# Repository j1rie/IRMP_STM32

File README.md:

# IRMP on STM32 - a USB IR receiver/sender/power switch with wake-up timer

A remote control receiver with many functions based on cheap hardware.

## Introduction
For 2 € you can buy an ST-Link emulator or a STM32F103 development board, usually made in China, on ebay. The STM32F103 microcontroller on it is flashed with an open source firmware with many functions.

## Features
* connection over USB 
* registers as HID device, appears as /dev/hidraw or "Custom HID device", no drivers needed
* transfers the data over USB2 in hardware at fullspeed 
* IR receiver (about 40 protocols decoded in hardware) 
* power on PC via remote control from S3 (STR) and S4 (STD) via USB or from S3, S4 and S5 (SoftOff) via motherboard switch (+5V required, on USB or from PSU or motherboard) 
* power on PC via built-in timer from S3 (STR) and S4 (STD) via USB or from S3, S4 and S5 (SoftOff) via motherboard switch (+5V required, on USB or from PSU or motherboard) 
* IR transmitter (about 40 protocols) 
* the configuration is stored in the emulated eeprom
* bootloader for easy firmware update
* macro support

A macro allows a sequence of IR commands to be sent via the transmitter diode when a trigger is received.
 macroslot0 is the trigger, macroslot1 … macroslot7 are the commands to be sent.

## Software Linux
* GUI configuration tool stm32IRconfig_gui for configuration: set, get and reset wakeup codes, macros, alarm time, send IR and show the received IR code. It is possible to program wakeups and macros by the remote control. Create, test and edit the translation table using remote control and mouse. Comprehensive debug messages. Firmware update.
* interactive command line program stm32IRconfig for configuration: set, get and reset wakeups, macros, alarm time, send IR and display the received IR code. It is possible to program wakeups and macros by the remote control.
* stm32IRalarm for setting and reading alarm time via script 
* stm32FWupgrade for command line firmware upgrade
* irmplircd is a daemon that runs in the background as an independent lirc server and passes the IR codes/events on to the application https://github.com/realglotzi/irmplircd
* irctl for configuration: https://github.com/olebowle/irctl
* Software available for Ubuntu, yaVDR, easyVDR, MLD.

## Software Windows
* GUI configuration tool stm32IRconfig_gui (same as linux)
* interactive command line programm stm32IRconfig (same as linux)
* stm32IRalarm to set and read alarm time via script
* stm32FWupgrade for command line firmware upgrade
* MediaPortal plugin: https://github.com/pikim/HIDIRT-host/tree/master/hidirt.MePo
* EventGhost with generic HID

## Creating a keymap
The stm32IRconfig_gui can be used to create a keymap using the remote control.  
There are two methods.  
  
(1)  
   
First method: Press "receive mode" and open the template keymap.
Click on the line with the name of the button, press the button on the remote, press "write IR" - repeat for all the buttons.  
  
(2)  
   
Second method: Press "receive mode".
Press the button on the remote, type the name of the button into the Key text box and press "append" - repeat for all the buttons.

You can now test the keymap: After pressing the button on the remote, the red cursor should be in the corresponding line.
When you are done, press "save" to save the keymap.

## Learning wakeup
If the first wakeup is empty, the first IR data received will be stored in the wakeup.  
Change wakeup with stm32kbdIRconfig_gui: press set by remote - wakeup, press button on remote control.  
Important for testing: wakeup only happens, if the PC is switched off.  
If the PC is powered on, only the key is sent to the PC (so you can use the same button to switch on and off).  

## EventGhost

A keycode in the left event window is dragged into the right configuration window and assigned to the desired action of a plugin. 

## Building from source
The sources are not complete until you run the prepare script, the script downloads the IRMP sources, extracts and patches the sources. You have to download the ST sources manually, because unfortunately you have to register.  
This makes it possible to put the patches under the GPL, without interfering with the original licences.  
It is also easier to see, what has been changed, too.  
Compile with arm-none-eabi-gcc.  

## Pin-Out
See /STM32Fxxxxx/src/config.h.

## Flashing the bootloader with a ST-Link
Connect  
Programmer SWDIO -> IO  
Programmer SWCLK -> CLK  
Programmer GND -> G  
Programmer 3V3 -> V3  
Windows:  
Get the STM32 ST-Link Utility.  
File - Open File - boot.blackDev.bin (https://github.com/j1rie/STM32F103-bootloader/tree/master/binaries)  
Target - Program & Verify (confirm a message about read out protection, if it appears)  
Linux:  
openocd -f ocd-program.cfg  
If the flash is locked, first run openocd -f ocd-unlock.cfg first, disconnect and reconnect the device, and then 
run openocd -f ocd-program.cfg again.  
The files are in the STM32Fxxx(yy)-bootloader repos.  
https://github.com/j1rie/IRMP_STM32_KBD/wiki/Herstellungsprozess-Schwarze#bootloader-flashen  

## Flashing the firmware
Disconnect from USB.  
Linux: Start ./stm32FWupgrade ./2019-07-06_16-32_blackDev_BL_SC_jrie.bin  
Windows: Start stm32FWupgrade.exe 2020-02-15_00-29_blueDev_BL_SC_jrie.bin  
Attach to USB.  
Instead of stm32FWupgrade you can use stm32IRconfig_gui.  
https://github.com/j1rie/IRMP_STM32_KBD/wiki/Herstellungsprozess-Schwarze#firmware-flashen  

## Other ways how to flash
Flashing with an USB-serial-TTL is possible on the developer boards.  
Flashing over USB is possible on the boards, that support it.  
See https://www.mikrocontroller.net/articles/IRMP_auf_STM32_-_ein_USB_IR_Empf%C3%A4nger/Sender/Einschalter_mit_Wakeup-Timer#Firmware_Flashing  

## irmplircd, eventlircd, udev and systemd
See /irmplircd/README.

## Schematics
https://datasheets.raspberrypi.com/pico/pico-datasheet.pdf  
https://datasheets.raspberrypi.com/pico/pico-2-datasheet.pdf  
https://files.waveshare.com/upload/4/4c/RP2040_Zero.pdf  
https://files.waveshare.com/upload/9/90/RP2040-One.pdf  
https://files.seeedstudio.com/wiki/XIAO-RP2350/res/Seeed-Studio-XIAO-RP2350-v1.0.pdf  

## Thanks to
Frank Meyer for IRMP. [1]  
Uwe Becker for adapting IRMP to the STM32F4xx and his USB-HID for the STM32F4xx. [2]  
His work helped me to get started with the STM32F105.  
Andrew Kambaroff for his USB-HID for the STM32F103. [3]  
His work helped me to get started with the STM32F103.  
Ole Ernst for code review, linux Makefile and linux download-extract-patch-script and new protocol. [4]  
Manuel Reimer for gcc-4.9 fix, SimpleCircuit and check if host is running. [5]  
Martin Neubauer for integration into EasyVDR, addon board development and selling ready-to-use receiver sets. [6]  
Alexander Grothe for integration into yaVDR and much help with difficult questions. [7]  
Helmut Emmerich for selling ready-to-use receiver sets and user support. [8]  
Claus Muus for integration into MLD. [9]  
Bernd Juraschek for vdr-plugin-statusleds, which was the base for vdr-plugin-statusleds2irmphidkbd. [10]  
All Users for questions, feature requests, feedback and ideas.  

[1] https://www.mikrocontroller.net/articles/IRMP  
[2] http://mikrocontroller.bplaced.net/wordpress/?page_id=744  
[3] https://habr.com/post/208026/  
[4] https://github.com/olebowle  
[5] https://github.com/M-Reimer  
[6] https://www.vdr-portal.de/user/4786-ranseyer/, https://github.com/ranseyer/STM32-IRMP-Hardware  
[7] https://www.vdr-portal.de/user/24681-seahawk1986/  
[8] https://www.vdr-portal.de/user/13499-emma53/  
[9] https://www.vdr-portal.de/user/942-clausmuus/  
[10] <statusleds@bjusystems.de>  

## Discussion and further information
Comments, questions and suggestions can be sent to https://www.vdr-portal.de/forum/index.php?thread/123572-irmp-auf-stm32-ein-usb-ir-empf%C3%A4nger-sender-einschalter-mit-wakeup-timer/

## Construction manuals
https://github.com/j1rie/IRMP_STM32_KBD/wiki/Herstellungsprozess-Schwarze  
https://www.mikrocontroller.net/articles/IRMP_auf_STM32_%E2%80%93_stark_vereinfachte_Bauanleitung  
https://www.mikrocontroller.net/articles/IRMP_auf_STM32_-_Bauanleitung  
The latter two are also in /doc/old.  

Have fun with IRMP on STM32!

Copyright (C) 2014-2025 Jörg Riechardt

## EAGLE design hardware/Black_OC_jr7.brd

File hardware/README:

There are different hardware designs for the sticks.
Make sure that the extension board fits your stick.

Stick1_jr1 is based on:
https://github.com/ranseyer/STM32-IRMP-Hardware/tree/master/1_Small_ST-Link/STl-Link-V303-small.brd
https://github.com/ranseyer/STM32-IRMP-Hardware/tree/master/1_Small_ST-Link/STl-Link-V303-small.sch

I highly recommend the optocoupler version. It is not very likely that you will actually need it, but
if you do have a motherboard, that needs it, it will save you a lot of debugging effort.

If you like a tiny design, have a look at https://github.com/Sl-Alex/IRMP_STM32_MINI and at
https://www.vdr-portal.de/index.php?attachment/48154-20230825-130009-jpg/

In case you want to attach a 4 digit display tm1637, connect:
GND - GND, 5V - 5V, DIO - B11, CLK - B4, see st32tm1637.h.

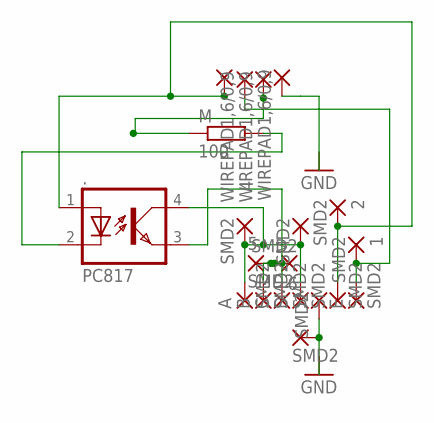
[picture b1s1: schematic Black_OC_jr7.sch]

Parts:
1, 2, 4, 5, 6, ...: SMD2; SMD1,27-2,54
+: SMD2; SMD1,27-2,54
-: SMD2; SMD1,27-2,54
--: 1,6/0,9
---: WIREPAD1,6/0,9; 1,6/0,9
----: WIREPAD1,6/0,9; 1,6/0,9
-----: WIREPAD1,6/0,9; 1,6/0,9
.: PC817; DIL04
A: SMD2; SMD1,27-2,54
B: SMD2; SMD1,27-2,54
C: SMD2; SMD1,27-2,54
D: SMD2; SMD1,27-2,54
E: SMD2; SMD1,27-2,54
M: 100; 0204/7
PAD7: SMD2; SMD1,27-2,54

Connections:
GND: -.1, -----.1, PAD7.1
unnamed: ----.1, M.1
unnamed: 4.1, ..4 (COL), ....1, A.1, D.1
unnamed: 5.1, 6.1, ..3 (EMIT), B.1, C.1
unnamed: 2.1, +.1, --.1, ..1 (A)
unnamed: 1.1, ---.1, E.1
unnamed: ..2 (C), M.2

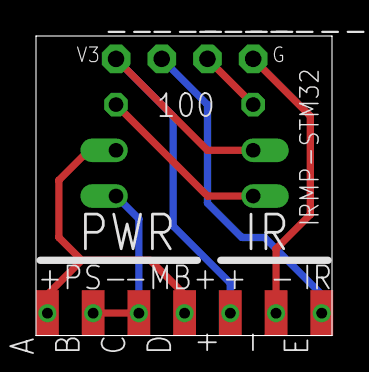
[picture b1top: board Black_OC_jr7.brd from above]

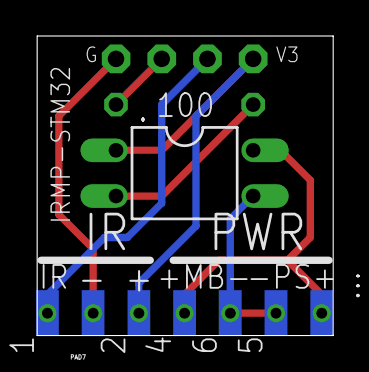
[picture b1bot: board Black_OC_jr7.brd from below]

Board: 2 copper layers, 16.4 x 16.6 mm, 20 parts (8 on the bottom side), 7 nets.

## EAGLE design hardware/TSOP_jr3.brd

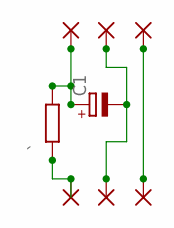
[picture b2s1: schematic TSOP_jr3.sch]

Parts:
": 1,6/0,9
"": 1,6/0,9
""": 1,6/0,9
...., ....., ......: 1,6/0,9
C1: CPOL-EUE1.8-4; E1,8-4
`: R-EU_0204/5; 0204/5

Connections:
unnamed: ".1, .......1
unnamed: "".1, ......1, C1.-
unnamed: """.1, C1.+, `.2
unnamed: .....1, `.1

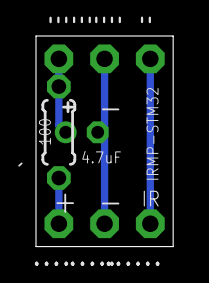
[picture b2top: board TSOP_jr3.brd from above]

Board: 2 copper layers, 7.6 x 11.7 mm, 8 parts (0 on the bottom side), 4 nets.

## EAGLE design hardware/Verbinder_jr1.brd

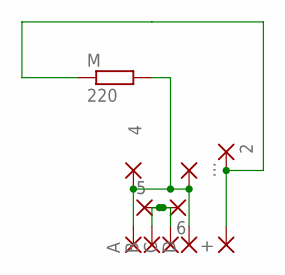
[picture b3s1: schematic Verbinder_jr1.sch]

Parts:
2, 4, 5, 6, ...: SMD2; SMD1,27-2,54
+: SMD2; SMD1,27-2,54
A: SMD2; SMD1,27-2,54
B: SMD2; SMD1,27-2,54
C: SMD2; SMD1,27-2,54
D: SMD2; SMD1,27-2,54
M: 220; 0204/7

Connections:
unnamed: 2.1, +.1, M.1
unnamed: 4.1, ....1, A.1, D.1, M.2
unnamed: 5.1, 6.1, B.1, C.1

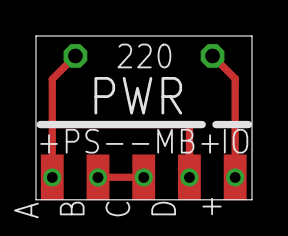
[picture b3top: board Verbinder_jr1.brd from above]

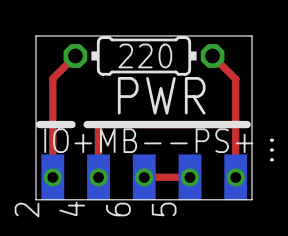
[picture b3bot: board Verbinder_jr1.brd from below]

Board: 2 copper layers, 12.0 x 9.1 mm, 11 parts (6 on the bottom side), 3 nets.

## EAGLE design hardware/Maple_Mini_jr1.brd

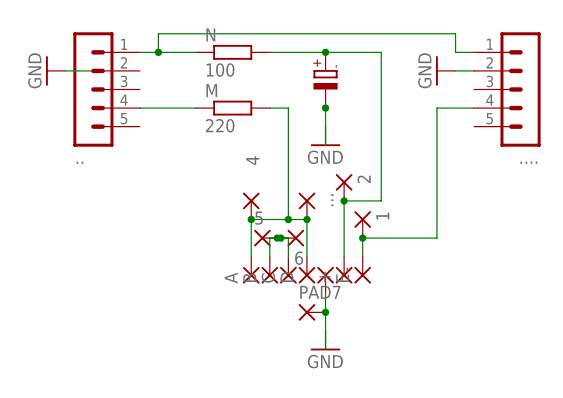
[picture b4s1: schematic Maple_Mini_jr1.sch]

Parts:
1, 2, 4, 5, 6, ...: SMD2; SMD1,27-2,54
+: SMD2; SMD1,27-2,54
-: SMD2; SMD1,27-2,54
.: CPOL-EUE1.8-4; E1,8-4
.., ....: MA05-1
A: SMD2; SMD1,27-2,54
B: SMD2; SMD1,27-2,54
C: SMD2; SMD1,27-2,54
D: SMD2; SMD1,27-2,54
E: SMD2; SMD1,27-2,54
M: 220; 0204/7
N: 100; 0204/7
PAD7: SMD2; SMD1,27-2,54

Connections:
GND: -.1, ..-, .....2, PAD7.1
unnamed: ...1, .....1, N.1
unnamed: ...4, M.1
unnamed: 4.1, ....1, A.1, D.1, M.2
unnamed: 5.1, 6.1, B.1, C.1
unnamed: 2.1, +.1, ..+, N.2
unnamed: 1.1, .....4, E.1

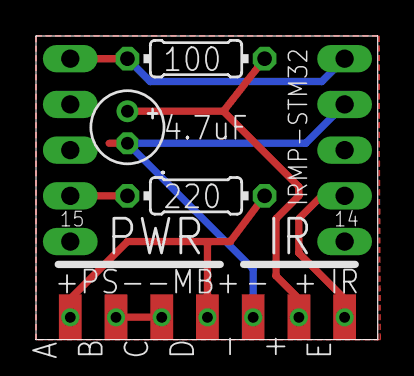
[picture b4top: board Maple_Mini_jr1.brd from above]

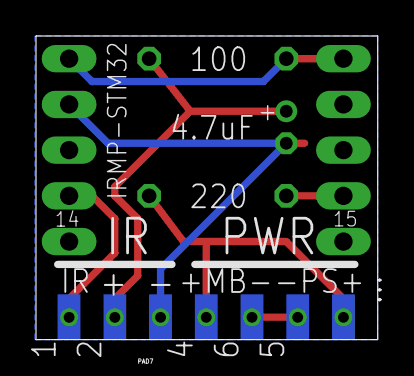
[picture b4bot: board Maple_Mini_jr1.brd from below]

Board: 2 copper layers, 19.0 x 16.9 mm, 19 parts (7 on the bottom side), 7 nets.

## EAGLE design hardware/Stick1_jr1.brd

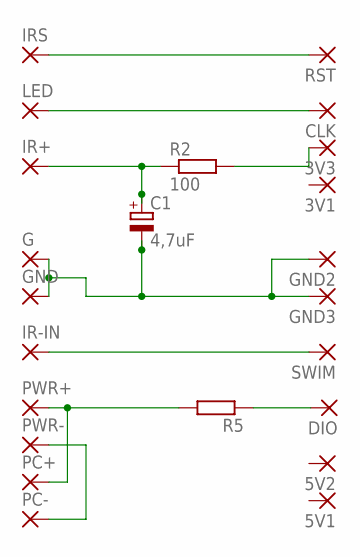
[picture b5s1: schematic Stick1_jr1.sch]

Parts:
3V1, 3V3, 5V1, 5V2: SMD2; SMD1,27-2,54
C1: 4,7uF; E1,8-4
CLK: SMD2; SMD1,27-2,54
DIO: SMD2; SMD1,27-2,54
G: SMD2; SMD1,27-2,54
GND, GND2, GND3: SMD2; SMD1,27-2,54
IR+: SMD2; SMD1,27-2,54
IR-IN: SMD2; SMD1,27-2,54
IRS: SMD2; SMD1,27-2,54
LED: SMD2; SMD1,27-2,54
PC+: SMD2; SMD1,27-2,54
PC-: SMD2; SMD1,27-2,54
PWR+: SMD2; SMD1,27-2,54
PWR-: SMD2; SMD1,27-2,54
R2: 100; 0204/7
R5: R-EU_0204/7; 0204/7
RST: SMD2; SMD1,27-2,54
SWIM: SMD2; SMD1,27-2,54

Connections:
unnamed: 3V3.1, R2.2
unnamed: C1.+, IR+.1, R2.1
unnamed: PC-.1, PWR-.1
unnamed: PC+.1, PWR+.1, R5.2
unnamed: DIO.1, R5.1
unnamed: CLK.1, LED.1
unnamed: IRS.1, RST.1
unnamed: IR-IN.1, SWIM.1
unnamed: C1.-, G.1, GND.1, GND2.1, GND3.1

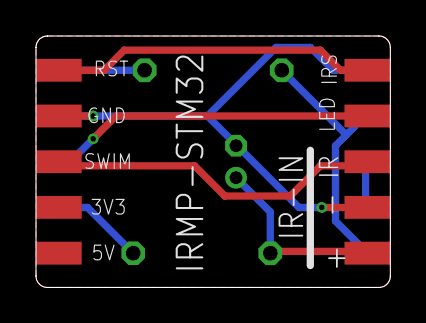
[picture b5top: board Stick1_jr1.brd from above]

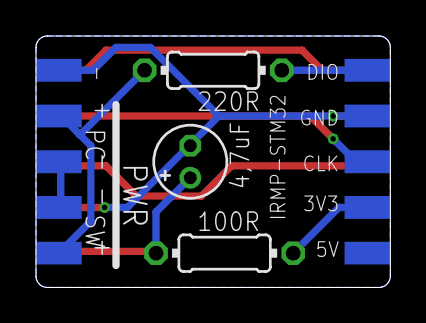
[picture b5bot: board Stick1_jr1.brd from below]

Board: 2 copper layers, 19.7 x 14.0 mm, 23 parts (13 on the bottom side), 9 nets.

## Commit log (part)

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2018-08-28 small fixes in text
2018-10-03 transfer to F105
2018-10-15 RCMM added to default
2018-10-15 fix warning
2018-11-02 new compiler wants spaces
2019-02-11 parameter change in dfu-util
2019-02-13 reset eeprom and firmware by flashing zeros
2019-05-04 updated dfu-util binary
2019-06-13 the --shutdown line in vdr.conf points to the shutdown script
2019-07-04 vdrshutdown example script
2019-07-06 removed forgotten line, improve irmpexec integration, make logging work
2019-07-06 imported more stuff from my mikrocontroller page into the README
2019-07-06 fix spelling
2019-07-06 formating
2019-07-06 spelling
2019-07-06 the F105 has been flashed so many times, that a new jumpaddress is necessary
2019-07-12 log only once
2019-07-12 improve description of macros
2019-07-12 make store_new_wakeup() faster
2019-07-13 point to github
2019-07-13 consume old IR before setting wakeup/macro by remote
2019-07-13 move 'consume old IR' into onReadIRcont()
2019-09-06 remove unneeded stuff from vdrshutdown script
2019-11-08 add ST-Link USB stick with unconnected PB11, fix typo, transfer to F105
2019-11-08 simplify ST-Link USB stick with unconnected PB11
2019-11-28 flashing bootloader and firmware
2019-11-28 link
2019-12-12 add F303 binaries
2019-12-12 adapt to F303
2019-12-14 fix eeprom and usb_hid patches
2019-12-20 make 'clean-objects' consistent
2019-12-20 make firmware string consistent
2020-01-22 use -ot instead of stat, exit with 1, thanks to @seahawk1986
2020-02-08 added connector board
2020-02-14 change blueDev pinout to blackdev pinout, firmwares, fix indentation
2020-02-15 recommend optocoupler
2020-02-18 add firmware flashing on Windows
2020-02-18 binaries
2020-02-26 pull from @a-v-s
2020-02-26 warn, if no STM32
2020-02-26 remove unneeded include
2020-03-04 fix error loop, when device gets disconnected, transfer to Windows, binaries
2020-04-16 added other ways of flashing
2020-04-18 remove ineffective attribute packed and unnecessary cast to enum
2020-04-22 linux gui: added firmware upgrade
2020-04-24 show update progress in gui as well, change pointer type
2020-04-25 indentation, one more sprintf
2020-04-29 change from libusb-0.1 to libusb-1.0
2020-05-01 change to USB-FS-Device_Lib_V4.1.0: adapt patches and script
2020-05-01 remove TODOs
2020-05-01 get wTransferSize from device instead from firmwae string
2020-05-07 collect messages which are to fast for gui, output to console too
2020-05-09 pointer argument for Upgrade needs to live longer, start thread earlier, initialize Upgrade, cleanup
2020-05-09 sleep not needed under linux
2020-05-20 loop longer in Write_and_Check(), silence warning, zstd needed for MSYS2 in Makefile, remove-O0 and -MD from Makefile, PATHSEP already defined, disconnect before rescan, show non-.bin files fully, Ct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
2020-05-20 tell used gcc-arm-none-eabi version, silence warning
2020-05-21 workaround for https://gcc.gnu.org/bugzilla/show_bug.cgi?id=83967, now newer gcc-arm-none-eabi versions do work
2020-05-21 initial start of stm32FWupgrade with files from @blacksphere/blackmagic/upgrade fetched Feb. 7, 2017
2020-05-21 change from libusb-0.1 to libusb-1.0, get wTransferSize from device, wait for device, firmwarefile as argument, remove -O0 and -MD from Makefile, remove unneeded includes
2020-05-22 binaries: stm32FWupgrade.exe, USB drivers for bootloader
2020-05-22 do without min(), merge includes for Windows and Linux
2020-05-27 no more sleep needed under Windows, simplify as bootloader is known, don't leak libusb_devices
2020-05-27 more simplify as bootloader is known, don't leak libusb_devices
2020-05-30 binaries, small fixes
2020-06-03 save debug messages, merge Makefiles for Windows and Linux, faster reconnect after reboot, -O2
2020-06-04 Windows binaries
2020-06-06 README: firmware update
2020-06-11 doc is old
2020-06-11 README: stm32FWupgrade, stm32IRconfig_gui
2020-06-14 use enum, better format using cast
2020-06-14 detection of HK32, thanks to @a-v-s
2020-06-17 small fixes
2020-06-17 no longer output whole romtable, simplify uC detection, only one char array for firmware, more fclose and free, small fixes
2020-06-24 firmwares, use sizeof(rt) instead of fixed size
2020-07-09 adapt IR.Bootloader.coproj to new gcc-arm-none-eabi versions
2020-07-09 bigger buffer for flashing ZEROS, avoid error in case of device without firmware
2020-07-09 bigger buffer for flashing ZEROS, avoid error in case of device without firmware for Linux as well
2020-07-09 transfer from F103 to F303
2020-07-16 F105: switch to USB On-The-Go Host and Device Lib V2.2.1: adapt patches and script, use symbolic constants in report descriptor, respond to configuration report ID only, workaround for https://gcc.gn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
2020-07-16 F303: switch to USB-FS-Device_Lib_V4.1.0: adapt patches and script, use symbolic constants in report descriptor, respond to configuration report ID only, workaround for https://gcc.gnu.org/bugzilla/s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
2020-07-18 F303: parts of the irmp.patch have been accepted into IRMP, so reduce patch accordingly
2020-07-21 fix hard to find stupid bug due to missing initialization, reduce scope, fix indentation, fix format, Makefile linux: remove -s
2020-08-15 adapt to IRMP 3.2.3
2020-11-15 forgotten firmwares, renamed yaVDR directories
2021-01-05 Fix prepare.bat for STM32F103
2021-01-05 file got renamed by ST, so adapt script
2021-01-07 Fix prepare.bat for STM32F105
2021-01-07 Fix irmp.patch for STM32F105
2021-01-08 Fix irmp.patch for STM32F303
2021-02-11 test suite and test mode in stm32IRconfig, more protocols
2021-02-16 update prepare.bat‘s (transfer from prepare.sh‘s), adapt to current IRMP/IRSND (#6) (#7)
    * Fix prepare.bat for STM32F103
    * Fix irmp.patch for STM32F103
    * Fix prepare.bat for STM32F105
    * Fix irmp.patch for STM32F105
    * Fix prepare.bat for STM32F303
    * Fix irmp.patch for STM32F303
2021-02-23 add STM32F401, binaries, use ORIGIN() and LENGTH() and comments in linker scripts
2021-03-16 example for irmpexec
2021-04-08 gcc 10 compatibility fix, transfer IR in-/output definitions to F105, fix comments
2022-01-12 firmware
2022-01-15 updated hidapi from https://github.com/libusb/hidapi, binaries for Windows
2022-01-22 comment on test conditions
2022-01-22 get IRMP from own repo, firmwares, support for 4-digit-display tm1637 based on @rogerdahl and @xamrex
2022-01-25 comment on IR receiver and connections for tm1637.h
2022-01-31 add again Make.config.template (why did I gitignore it?)
2022-01-31 add comment on new extension board into Make.config.template
2022-03-19 improve hid test, print only necessary bytes, sleep longer, transfer linux to Windows, use constants from firmware, minor fixes
2022-03-19 print only necessary bytes on Windows as well
2022-03-24 get report count from firmware, show only relevant bytes
2022-04-23 invert EXTLED logic, make 4-digit-display conditional, clean up, gui binary
2022-07-14 add new firmwares with RC6A20 and RC6A28 (Sky+ and Sky Q), delete old firmwares
2022-07-15 cleanup scripts
2022-07-15 fix rom and ram length and other minor fixes
2022-07-15 update hidapi from @libusb
2022-07-21 implement eeprom reset and minor fixes
2022-07-23 more eeprom reset, use SCNx8 for uint8_t, use toUInt and FXUIntVal for unsigned values
2022-09-01 fix Read(), improve Write(), more thorough compare in Write_and_Check(), cleanup, silence warnings, fix being stuck after IR reception while host not running
2022-09-03 wait for previous transfer to complete and check if host is running for send_magic() as well
2023-04-08 add eeprom commit, fix typos, minor fixes
2023-04-08 start STM32F103xC as copy of STM32F103x8
2023-04-11 explain the name, add flashing with linux
2023-04-11 fix not reading full lenght resulted in subsequent errors, minor fixes
2023-04-13 more get report count from report descriptor and double-check with report count from firmware, update hidapi
2023-04-21 add RP2040
2023-04-28 firmware for F103CC, set maximum output current for WAKEUP_PIN
2023-04-29 improve detection if host is running
2023-05-12 reset PrevXferComplete entering Suspend Mode and remove WKUP_Callback for F103
2023-05-13 transfer to other uC
2023-05-17 commit first received IR code to eeprom
2023-05-27 commit first wakeup to eeprom, if set by config app, validation is only needed in eeprom_commit()
2023-05-27 fix typo
2023-06-07 don't send USB data, if not configured
2023-06-08 fix forgotten entry
2023-06-14 improve condition for Wakeup() and for USB_HID_SendData(), small fixes and improvements
2023-06-16 put conditions into function USB_Ready(), small fixes and improvements
2023-07-07 use PrevXferComplete in RP2040 too, fix handling full in eeprom_begin(), improve eeprom_reset() so eeprom_begin is not needed afterwards
2023-07-28 point to Microsoft Visual C++ Redistributable
2023-12-29 reset IRSND_BIT for RP2040
2023-12-29 reset IRSND_BIT for RP2040, part 2
2024-01-11 statusled
2024-01-11 app for switching statusled on/off
2024-01-12 increase buffer size, simlify, typo
2024-01-14 statusled for F103+F105, fix stm32IRstatusled: -d needs an argument
2024-01-16 statusled for F303+F401
2024-01-16 firmwares, minor fixes
2024-01-18 README for vdr + vdr-plugin-statusleds + stm32IRstatusled, statusled for GreenLink
2024-01-18 change statusled pin for RP2040-One
2024-03-27 build for several boards
2024-03-27 use RGB-LED as status LED
2024-03-27 mention One and Zero pins
2024-04-12 describe neopixel protocol, add command neopixel, tune colors, tune timings, add neopixel test and set neopixel
2024-04-17 simplify, cleanup
2024-04-17 update READMEs, cleanup Makefiles, improve stm32IRconfig text
2024-04-20 show macros at connect, cleanup
2024-04-20 describe macro configuration with stm32IRconfig_gui, cleanup
2024-04-23 describe macros
2024-09-07 support RP235x, rename RP2040 to RP2xxx because of RP235x, small fixes, cleanup
2024-09-11 firmwares built with master instead of develop
2024-09-12 update RP2xxx README
2024-10-09 update hidapi from @libusb, binaries
2024-11-15 rewrite README with input from DeepL Write
2024-11-15 rewrite READMEs with input from DeepL Write
2024-11-16 LIESMICH
2024-11-16 further improve README and LIESMICH
2024-11-28 Seeed XIAO RP2350
2024-12-18 README, LIESMICH
2025-01-29 more colors, show USB status via RGB LED, update Windows stm32IRconfig, README+LIESMICH: RGB-LED colors and images, stm32IRconfig binaries, firmware
2025-02-11 fixes for stm32IRconfig, link for Gentoo integration
2025-02-18 fix 0436f85
2025-03-13 use fastest supported clock, use picotool for firmware upgrade on RP2xxx
2025-04-16 firmwares, make firmware string and filename consistent
2025-04-16 new line
2025-04-17 led table
2025-04-24 make send_after_wakeup configurable, simplify CMakeLists.txt, README, LIESMICH, ws2812.pio.h might have the wrong pio version, so delete it before building again, firmwares
2025-05-09 support APA106
2025-05-14 MAKROS.md and MACROS.md, LIESMICH.md and README.md, PROTOCOLS.md
2025-05-17 windows binary
2025-05-21 fix systick clock, firmware
2025-06-07 don’t filter repeat, let VDR do it
2025-06-18 more thanks
2025-06-18 formatting
2025-06-25 vdr-plugin-irmplirc
2025-06-27 more work on vdr-plugin-irmplirc
2025-06-27 reset repeat rate at protocol change
2025-06-28 make code look like IRMP data
2025-08-05 transmission last macro, when the alarm timer expires
2025-08-20 set RepeatRate only if repeat
2025-08-23 change icon
2025-09-17 implement eeprom dirty and show message on disconnect and close, if eeprom is dirty
2025-10-07 implement thread to filter out config reports, update LIESMICH and README
2025-10-08 fix missing item
2025-10-29 fix key creation and magic key
2025-11-08 show version (as date of compilation)
2025-11-09 show version (as date of compilation) part 3
2025-11-12 let the LEDs shine during firmware upgrade
2025-12-18 overclock the RP2350 a little
2025-12-18 autodetect repeatrate and derive repetition in IRMP
2026-01-15 make compatible with IRMP_PICO
2026-03-05 add repeat rate statistics to irmpconfig, add links to schematics, delay in between sending macros, update IRMP, include IRMP_TECHNICS_PROTOCOL in test-suite, set drive strength of IR_OUT_GPIO to 12 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
2026-03-06 stm32IRconfig Linux and Windows, binaries
2026-03-07 use macro, pass on delta detection, simplify report descriptor
